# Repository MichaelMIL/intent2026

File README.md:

# INTENT 2026 Hardware Badge

RP2040 conference badge for the INTENT 2026 security summit, shaped like a vending machine: a header sign
with the lanyard holes, the cabinet with the product window, keypad and item-pickup door, and a pedestal.
56 × 100 mm, two layers, purple solder mask, with three **breakaway soda-can modules** (IR receiver,
audio jack, speaker) that snap off and plug back into slots on the badge.

Board rev **0.5** (2026-10-11). Fab target: JLCPCB, Standard PCBA.

<p align="center">
  
  &nbsp;&nbsp;&nbsp;
  
</p>

## Schematic

- **PDF:** [04-fab/intent-2026-badge-schematic.pdf](04-fab/intent-2026-badge-schematic.pdf)
- Source: [03-kicad/intent-2026-badge.kicad_sch](03-kicad/intent-2026-badge.kicad_sch) (generated, see below)

## What is on the board

| Block | Parts |
|---|---|
| MCU | RP2040 (U1), 16 Mbit QSPI flash (U2), 12 MHz crystal, BOOTSEL key SW1 |
| USB | USB-C receptacle (J1), USBLC6-2 ESD array, 27 Ω series resistors |
| Power | USB or 3×AAA battery (J3) through a P-MOSFET / Schottky power path, ME6206 3.3 V LDO |
| User interface | Keys A / B / C (GPIO4 / 3 / 2), five red "credit" LEDs (GPIO5–9), four WS2812B-2020 RGB LEDs on the shelf (GPIO10) |
| Hack header | J2, 2×13 pins (not fitted): 15 GPIO, SWD, RUN, 3V3, GND, RGB chain out; UART0 on test pads TX / RX / GND |
| Expansion slots | J5 **IR** (GPIO22), J6 **AUDIO** (GPIO11), J7 **SPK** (GPIO25). 1×3 sockets, pin 1 = GND, 2 = 3V3, 3 = signal |

### Breakaway modules

The three modules are 13 × 22 mm soda cans hanging under the pedestal on 4 mm tabs with mouse bites. Snap them off, then plug each one
into its slot. Every port has the same pinout (GND / 3V3 / signal, power in the middle), so a module plugged
in backwards swaps ground and signal and never puts 3V3 on a GPIO.

The artwork plays along: the INTENT logo, the INTENT-O-MATIC marquee, the key letters and the can rims are exposed
copper (gold with ENIG), the RGB LEDs glow inside drawn products (can, cup, chips, candy bar) on a shelf with price tags
and a dispensing coil, the keys sit in a SELECT bezel, the five red LEDs are the CREDIT meter, the module slots are the
ITEM PICKUP door, the UART test pads are the coins, and the cabinet stands on two feet. The back shows the three AAA
cells where the battery box goes, a DANGER 3V3 sticker and a service log. The modules are the vended drinks.

| Item | Module | Circuit | Slot |
|---|---|---|---|
| B1 "IR COLA" | IR | Everlight IRM-H638T 38 kHz receiver with RC supply filter | J5, GPIO22 |
| B2 "AUDIO POP" | AUDIO | 3.5 mm TRRS jack behind a 1 k / 10 n PWM low-pass and 10 µF DC block | J6, GPIO11 (PWM) |
| B3 "BEEP FIZZ" | SPK | MLT-8530 magnetic transducer, S8050 low-side driver, flyback diode | J7, GPIO25 (2.7 kHz square wave) |

## Repository layout

| Folder | Content |
|---|---|
| `00-bom/` | Priced BOM (B2) and the change log on top of it (`bom-deltas.md`, Hebrew mirror) |
| `01-spec/` | Design spec: outline, power tree, net list, GPIO map, modules |
| `02-layout/` | Placement plan, front/back mockups, logo artwork |
| `03-kicad/` | KiCad project **and the scripts that generate it** (see `BUILD-NOTES.md`) |
| `04-fab/` | Gerbers, JLC BOM/CPL, DRC/ERC reports, renders, schematic PDF, order spec |
| `05-firmware-notes/` | GPIO map and notes for the firmware |

## How the design is built

The KiCad files are generated, not hand-drawn:

- `03-kicad/scripts/design.py` is the netlist (parts, pins, nets, LCSC numbers).
- `placement.py` holds every coordinate, including the module rectangles and tabs.
- `gen_sch.py` draws the wired schematic, `pcb_build.py` creates the board and outline,
  `router/route2.py` routes it, `pcb_finish.py` adds pours and silkscreen, `fab_export.py` writes the JLC files.
- `check_sch.py --erc` proves the schematic matches `design.py` pin for pin and runs ERC.

Current status: ERC 0 errors, DRC 0 violations and 0 unconnected pads (KiCad 10.0.3).
Order details and the pre-order checklist are in [`04-fab/order-spec.md`](04-fab/order-spec.md).

## Team

Idan Ben Moshe, Matar Maoz, Benny Mizels, Michael Mark, Mattar Bernhard, Tomer Zait.

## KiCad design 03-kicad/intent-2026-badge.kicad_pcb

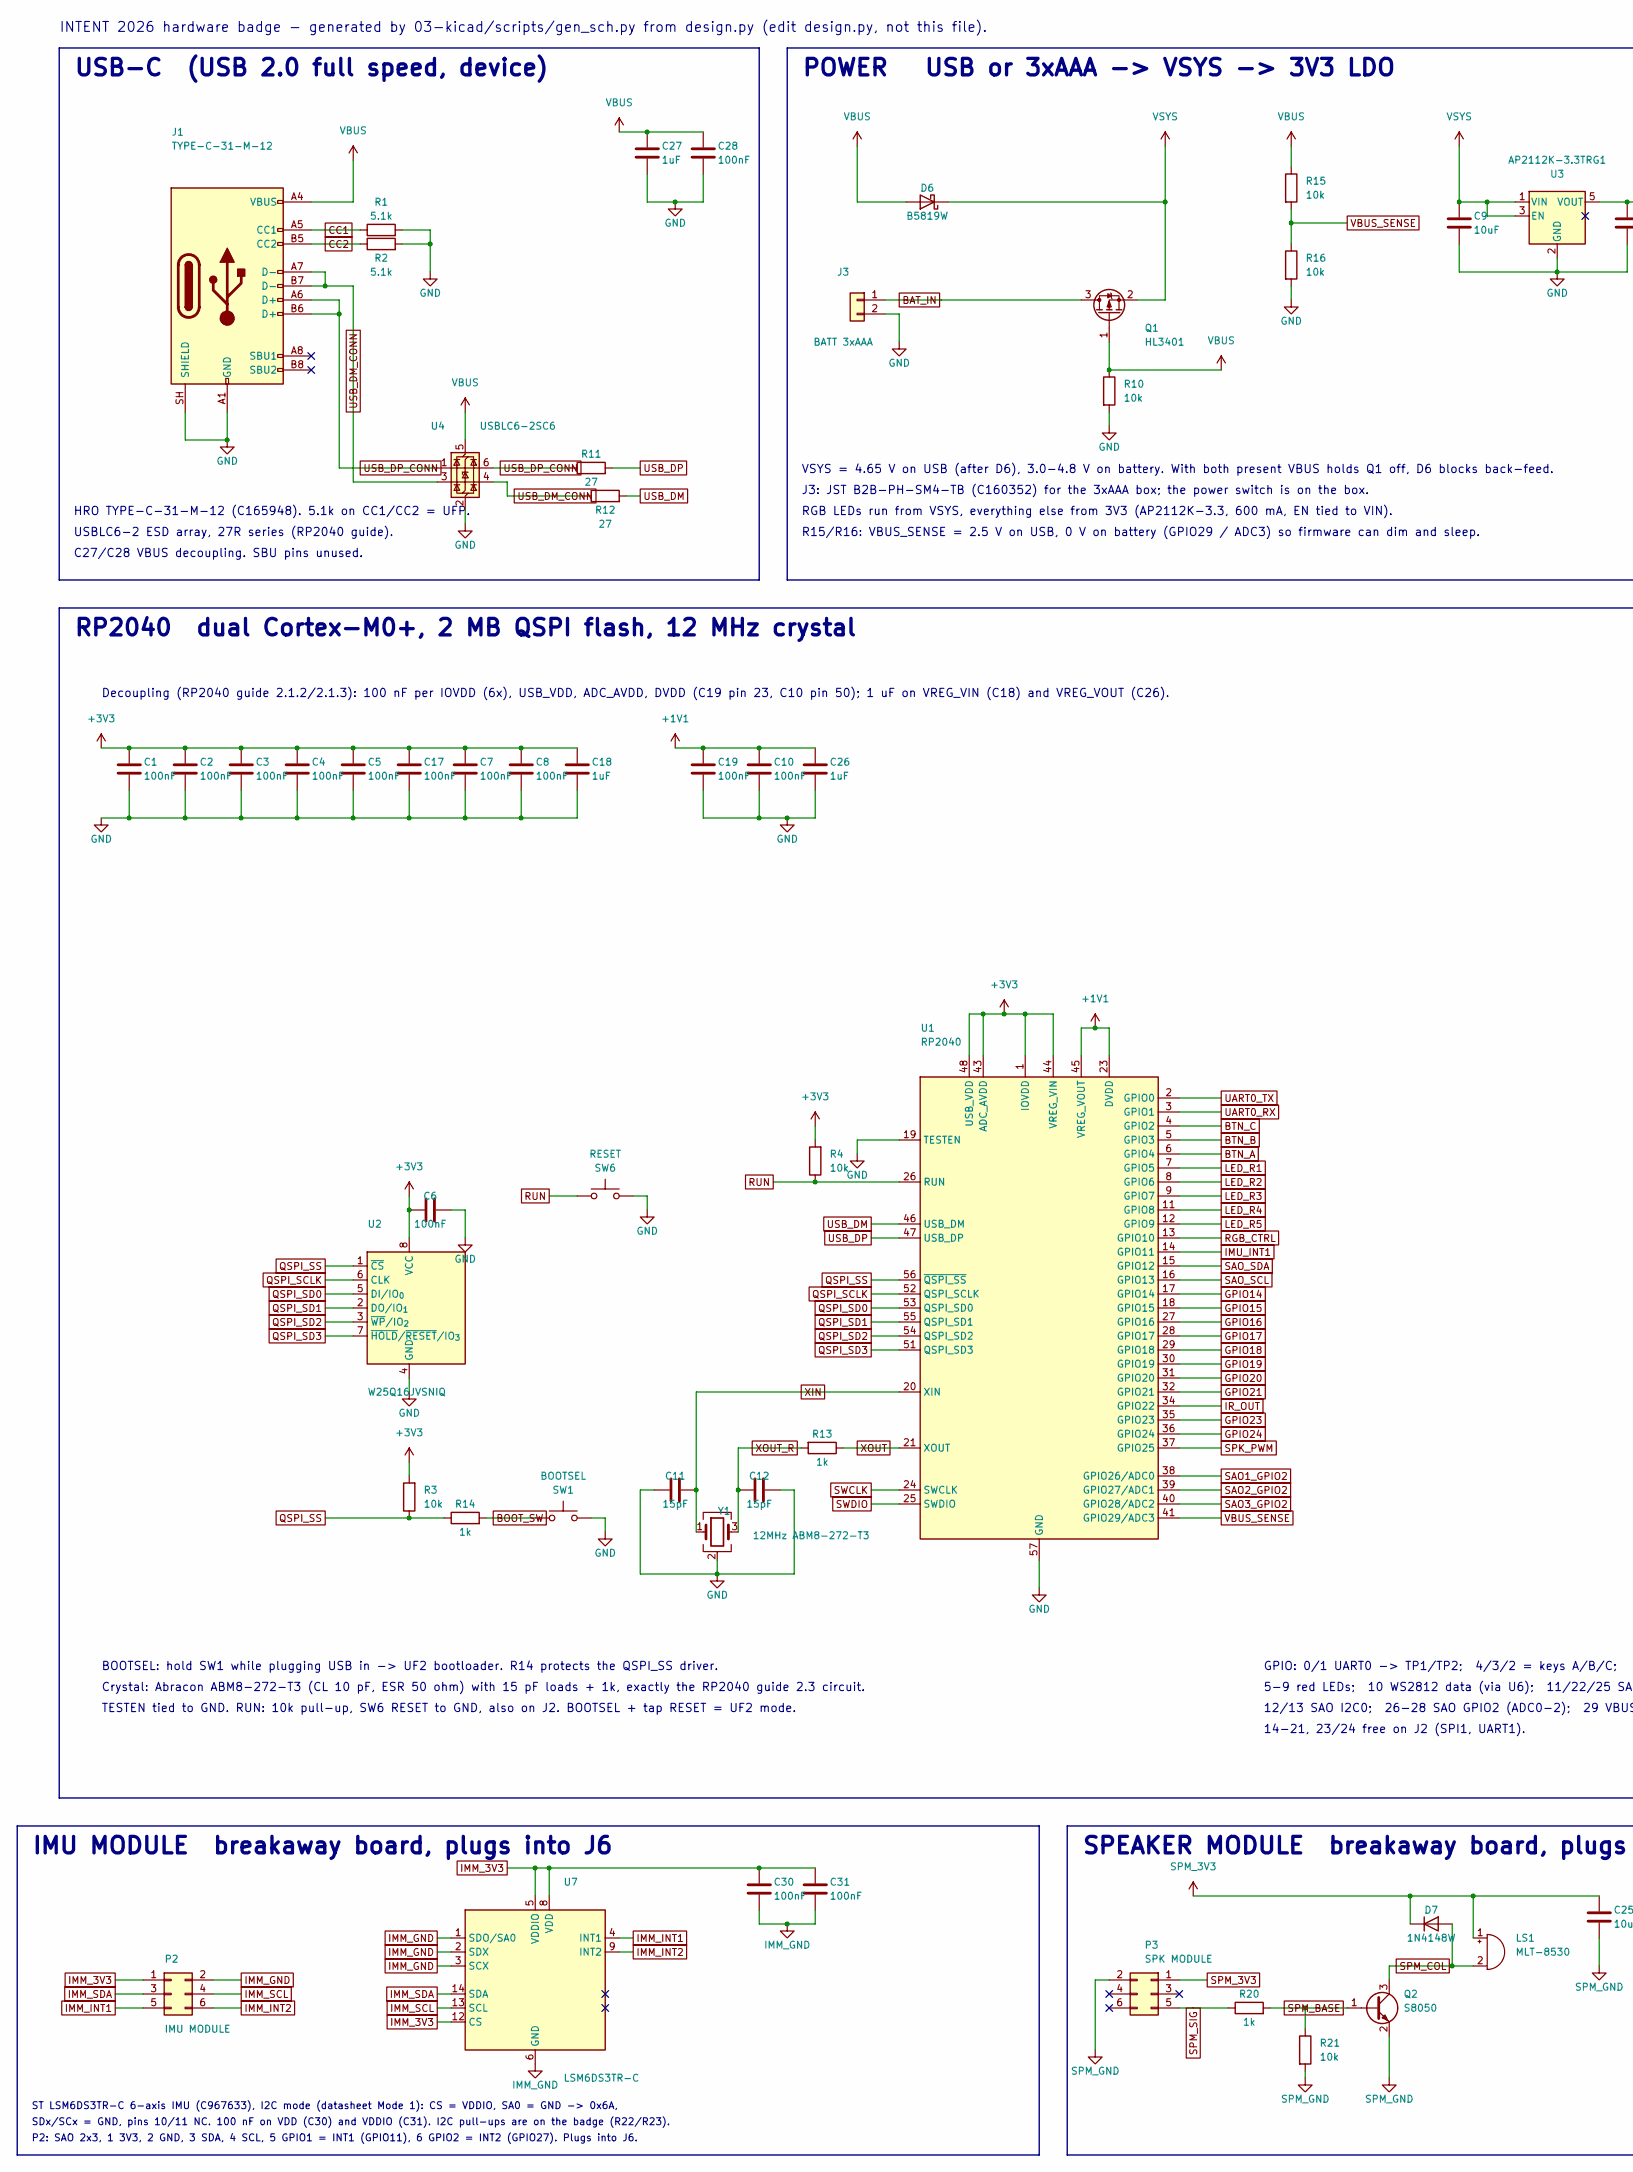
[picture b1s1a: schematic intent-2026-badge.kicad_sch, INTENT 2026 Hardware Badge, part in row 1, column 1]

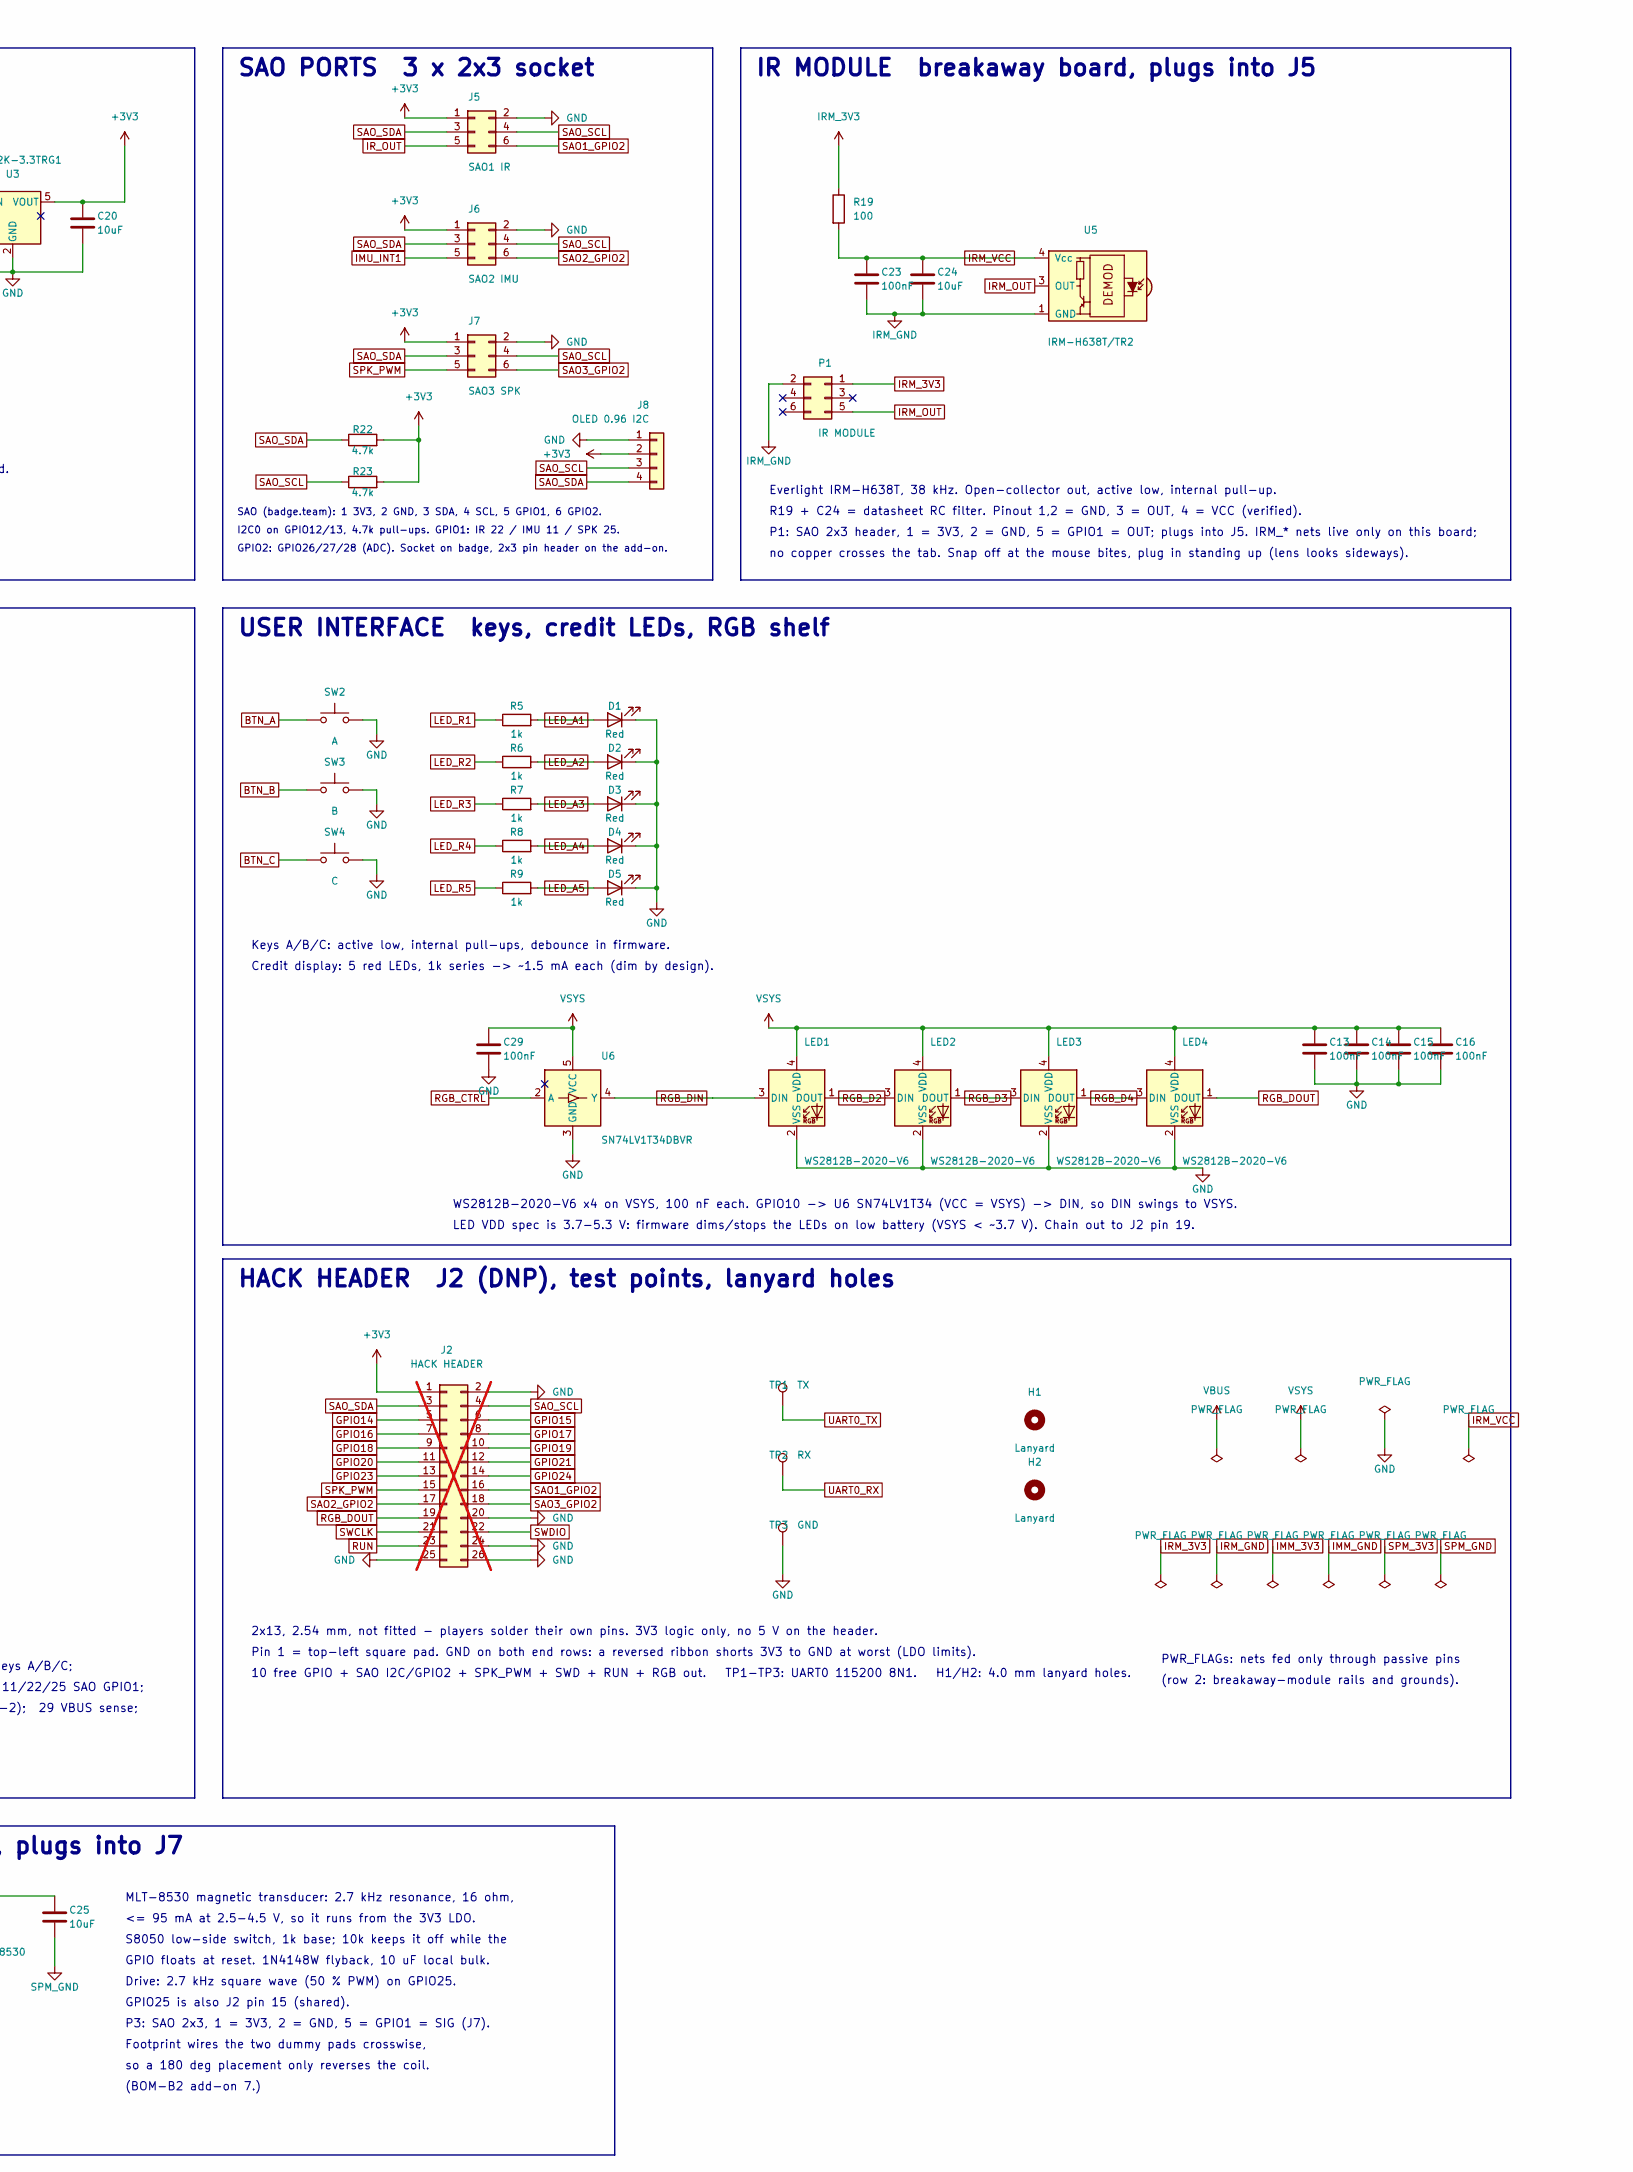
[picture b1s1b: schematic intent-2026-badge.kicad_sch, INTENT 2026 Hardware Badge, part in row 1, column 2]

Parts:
C1, C2, C3, C4, C5, C6, C7, C8, C10, C13, C14, C15, C16, C17, C19, C23, C28, C29, C30, C31: 100nF; C_0402_1005Metric; LCSC C60474
C9, C20, C24, C25: 10uF; C_0805_2012Metric; LCSC C7503495
C11, C12: 15pF; C_0402_1005Metric; LCSC C1548
C18, C26, C27: 1uF; C_0402_1005Metric; LCSC C6119792
D1, D2, D3, D4, D5: Red; LED_0603_1608Metric; LCSC C2286
D6: B5819W; D_SOD-123; LCSC C7420330
D7: 1N4148W; D_SOD-123; LCSC C81598
H1, H2: Lanyard; LanyardHole_4.0mm_Plated
J1: TYPE-C-31-M-12; USB_C_Receptacle_HRO_TYPE-C-31-M-12; LCSC C165948
J2: HACK HEADER; PinHeader_2x13_P2.54mm_Vertical; not fitted
J3: BATT 3xAAA; JST_PH_B2B-PH-SM4-TB_1x02-1MP_P2.00mm_Vertical; LCSC C160352
J5: SAO1 IR; PinSocket_2x03_P2.54mm_Vertical_SMD; LCSC C42163131
J6: SAO2 IMU; PinSocket_2x03_P2.54mm_Vertical_SMD; LCSC C42163131
J7: SAO3 SPK; PinSocket_2x03_P2.54mm_Vertical_SMD; LCSC C42163131
J8: OLED 0.96 I2C; PinSocket_1x04_P2.54mm_Vertical_SMD_Pin1Right; LCSC C42379197
LED1, LED2, LED3, LED4: WS2812B-2020-V6; LED_WS2812B-2020_PLCC4_2.0x2.0mm; LCSC C52917434
LS1: MLT-8530; Buzzer_MLT-8530_C94599; LCSC C94599
P1: IR MODULE; PinHeader_2x03_P2.54mm_Vertical_SMD; LCSC C3294461
P2: IMU MODULE; PinHeader_2x03_P2.54mm_Vertical_SMD; LCSC C3294461
P3: SPK MODULE; PinHeader_2x03_P2.54mm_Vertical_SMD; LCSC C3294461
Q1: HL3401; SOT-23; LCSC C22469449
Q2: S8050; SOT-23; LCSC C2146
R1, R2: 5.1k; R_0402_1005Metric; LCSC C25905
R3, R4, R10, R15, R16, R21: 10k; R_0402_1005Metric; LCSC C25744
R5, R6, R7, R8, R9, R13, R14, R20: 1k; R_0402_1005Metric; LCSC C11702
R11, R12: 27; R_0402_1005Metric; LCSC C25100
R19: 100; R_0402_1005Metric; LCSC C25076
R22, R23: 4.7k; R_0402_1005Metric; LCSC C25900
SW1: BOOTSEL; SW_Push_1P1T_XKB_TS-1187A; LCSC C318884
SW2: A; SW_Push_1P1T_XKB_TS-1187A; LCSC C318884
SW3: B; SW_Push_1P1T_XKB_TS-1187A; LCSC C318884
SW4: C; SW_Push_1P1T_XKB_TS-1187A; LCSC C318884
SW6: RESET; SW_Push_1P1T_XKB_TS-1187A; LCSC C318884
TP1: TX; TestPoint_THTPad_D1.5mm_Drill0.7mm
TP2: RX; TestPoint_THTPad_D1.5mm_Drill0.7mm
TP3: GND; TestPoint_THTPad_D1.5mm_Drill0.7mm
U1: RP2040; QFN-56-1EP_7x7mm_P0.4mm_EP3.2x3.2mm; LCSC C2040
U2: W25Q16JVSNIQ; SOIC-8_3.9x4.9mm_P1.27mm; LCSC C2456211
U3: AP2112K-3.3TRG1; SOT-23-5; LCSC C51118
U4: USBLC6-2SC6; SOT-23-6; LCSC C2827654
U5: IRM-H638T/TR2; IRM-H638T_C91447; LCSC C91447
U6: SN74LV1T34DBVR; SOT-23-5; LCSC C100024
U7: LSM6DS3TR-C; LGA-14_3x2.5mm_P0.5mm_LayoutBorder3x4y; LCSC C967633
Y1: 12MHz ABM8-272-T3; Crystal_SMD_3225-4Pin_3.2x2.5mm; LCSC C20625731

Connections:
+1V1: C10.1, C19.1, C26.1, U1.23 (DVDD), U1.45 (VREG_VOUT), U1.50 (DVDD)
+3V3: C1.1, C2.1, C3.1, C4.1, C5.1, C6.1, C7.1, C8.1, C17.1, C18.1, C20.1, J2.1, J5.1, J6.1, J7.1, J8.2, R3.2, R4.2, R22.2, R23.2, U1.1 (IOVDD), U1.10 (IOVDD), U1.22 (IOVDD), U1.33 (IOVDD), U1.42 (IOVDD), U1.43 (ADC_AVDD), U1.44 (VREG_VIN), U1.48 (USB_VDD), U1.49 (IOVDD), U2.8 (VCC), U3.5 (VOUT)
BAT_IN: J3.1, Q1.3 (D)
BOOT_SW: R14.2, SW1.1
BTN_A: SW2.1, U1.6 (GPIO4)
BTN_B: SW3.1, U1.5 (GPIO3)
BTN_C: SW4.1, U1.4 (GPIO2)
CC1: J1.A5 (CC1), R1.1
CC2: J1.B5 (CC2), R2.1
GND: C1.2, C2.2, C3.2, C4.2, C5.2, C6.2, C7.2, C8.2, C9.2, C10.2, C11.2, C12.2, C13.2, C14.2, C15.2, C16.2, C17.2, C18.2, C19.2, C20.2, C26.2, C27.2, C28.2, C29.2, D1.1 (K), D2.1 (K), D3.1 (K), D4.1 (K), D5.1 (K), J1.A1 (GND), J1.A12 (GND), J1.B1 (GND), J1.B12 (GND), J1.SH (SHIELD), J2.2, J2.20, J2.24, J2.25, J2.26, J3.2, J5.2, J6.2, J7.2, J8.1, LED1.2 (VSS), LED2.2 (VSS), LED3.2 (VSS), LED4.2 (VSS), R1.2, R2.2, R10.2, R16.2, SW1.2, SW2.2, SW3.2, SW4.2, SW6.2, TP3.1 (1_1), U1.19 (TESTEN), U1.57 (GND), U2.4 (GND), U3.2 (GND), U4.2 (GND), U6.3 (GND), Y1.2 (G), Y1.4 (G)
GPIO14: J2.5, U1.17 (GPIO14)
GPIO15: J2.6, U1.18 (GPIO15)
GPIO16: J2.7, U1.27 (GPIO16)
GPIO17: J2.8, U1.28 (GPIO17)
GPIO18: J2.9, U1.29 (GPIO18)
GPIO19: J2.10, U1.30 (GPIO19)
GPIO20: J2.11, U1.31 (GPIO20)
GPIO21: J2.12, U1.32 (GPIO21)
GPIO23: J2.13, U1.35 (GPIO23)
GPIO24: J2.14, U1.36 (GPIO24)
IMM_3V3: C30.1, C31.1, P2.1, U7.5 (VDDIO), U7.8 (VDD), U7.12 (CS)
IMM_GND: C30.2, C31.2, P2.2, U7.1 (SDO/SA0), U7.2 (SDX), U7.3 (SCX), U7.6 (GND), U7.7 (GND)
IMM_INT1: P2.5, U7.4 (INT1)
IMM_INT2: P2.6, U7.9 (INT2)
IMM_SCL: P2.4, U7.13 (SCL)
IMM_SDA: P2.3, U7.14 (SDA)
IMU_INT1: J6.5, U1.14 (GPIO11)
IRM_3V3: P1.1, R19.1
IRM_GND: C23.2, C24.2, P1.2, U5.1 (GND), U5.2 (GND)
IRM_OUT: P1.5, U5.3 (OUT)
IRM_VCC: C23.1, C24.1, R19.2, U5.4 (Vcc)
IR_OUT: J5.5, U1.34 (GPIO22)
LED_A1: D1.2 (A), R5.2
LED_A2: D2.2 (A), R6.2
LED_A3: D3.2 (A), R7.2
LED_A4: D4.2 (A), R8.2
LED_A5: D5.2 (A), R9.2
LED_R1: R5.1, U1.7 (GPIO5)
LED_R2: R6.1, U1.8 (GPIO6)
LED_R3: R7.1, U1.9 (GPIO7)
LED_R4: R8.1, U1.11 (GPIO8)
LED_R5: R9.1, U1.12 (GPIO9)
QSPI_SCLK: U1.52 (QSPI_SCLK), U2.6 (CLK)
QSPI_SD0: U1.53 (QSPI_SD0), U2.5 (DI/IO_{0})
QSPI_SD1: U1.55 (QSPI_SD1), U2.2 (DO/IO_{1})
QSPI_SD2: U1.54 (QSPI_SD2), U2.3 (~WP/IO_{2})
QSPI_SD3: U1.51 (QSPI_SD3), U2.7 (~HOLD/~RESET/IO_{3})
QSPI_SS: R3.1, R14.1, U1.56 (~QSPI_SS), U2.1 (~CS)
RGB_CTRL: U1.13 (GPIO10), U6.2 (A)
RGB_D2: LED1.1 (DOUT), LED2.3 (DIN)
RGB_D3: LED2.1 (DOUT), LED3.3 (DIN)
RGB_D4: LED3.1 (DOUT), LED4.3 (DIN)
RGB_DIN: LED1.3 (DIN), U6.4 (Y)
RGB_DOUT: J2.19, LED4.1 (DOUT)
RUN: J2.23, R4.1, SW6.1, U1.26 (RUN)
SAO1_GPIO2: J2.16, J5.6, U1.38 (GPIO26/ADC0)
SAO2_GPIO2: J2.17, J6.6, U1.39 (GPIO27/ADC1)
SAO3_GPIO2: J2.18, J7.6, U1.40 (GPIO28/ADC2)
SAO_SCL: J2.4, J5.4, J6.4, J7.4, J8.3, R23.1, U1.16 (GPIO13)
SAO_SDA: J2.3, J5.3, J6.3, J7.3, J8.4, R22.1, U1.15 (GPIO12)
SPK_PWM: J2.15, J7.5, U1.37 (GPIO25)
SPM_3V3: C25.1, D7.1 (K), LS1.1 (+), P3.1
SPM_BASE: Q2.1 (B), R20.2, R21.1
SPM_COL: D7.2 (A), LS1.2 (-), Q2.3 (C)
SPM_GND: C25.2, P3.2, Q2.2 (E), R21.2
SPM_SIG: P3.5, R20.1
SWCLK: J2.21, U1.24 (SWCLK)
SWDIO: J2.22, U1.25 (SWDIO)
UART0_RX: TP2.1 (1_1), U1.3 (GPIO1)
UART0_TX: TP1.1 (1_1), U1.2 (GPIO0)
USB_DM: R12.2, U1.46 (USB_DM)
USB_DM_CONN: J1.A7 (D-), J1.B7 (D-), R12.1, U4.3 (I/O2), U4.4 (I/O2)
USB_DP: R11.2, U1.47 (USB_DP)
USB_DP_CONN: J1.A6 (D+), J1.B6 (D+), R11.1, U4.1 (I/O1), U4.6 (I/O1)
VBUS: C27.1, C28.1, D6.2 (A), J1.A4 (VBUS), J1.A9 (VBUS), J1.B4 (VBUS), J1.B9 (VBUS), Q1.1 (G), R10.1, R15.1, U4.5 (VBUS)
VBUS_SENSE: R15.2, R16.1, U1.41 (GPIO29/ADC3)
VSYS: C9.1, C13.1, C14.1, C15.1, C16.1, C29.1, D6.1 (K), LED1.4 (VDD), LED2.4 (VDD), LED3.4 (VDD), LED4.4 (VDD), Q1.2 (S), U3.1 (VIN), U3.3 (EN), U6.5 (VCC)
XIN: C11.1, U1.20 (XIN), Y1.1
XOUT: R13.1, U1.21 (XOUT)
XOUT_R: C12.1, R13.2, Y1.3

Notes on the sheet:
USB-C (USB 2.0 full speed, device)
HRO TYPE-C-31-M-12 (C165948). 5.1k on CC1/CC2 = UFP.
USBLC6-2 ESD array, 27R series (RP2040 guide).
C27/C28 VBUS decoupling. SBU pins unused.
POWER USB or 3xAAA -> VSYS -> 3V3 LDO
VSYS = 4.65 V on USB (after D6), 3.0-4.8 V on battery. With both present VBUS holds Q1 off, D6 blocks back-feed.
J3: JST B2B-PH-SM4-TB (C160352) for the 3xAAA box; the power switch is on the box.
RGB LEDs run from VSYS, everything else from 3V3 (AP2112K-3.3, 600 mA, EN tied to VIN).
R15/R16: VBUS_SENSE = 2.5 V on USB, 0 V on battery (GPIO29 / ADC3) so firmware can dim and sleep.
SAO PORTS 3 x 2x3 socket
SAO (badge.team): 1 3V3, 2 GND, 3 SDA, 4 SCL, 5 GPIO1, 6 GPIO2.
I2C0 on GPIO12/13, 4.7k pull-ups. GPIO1: IR 22 / IMU 11 / SPK 25.
GPIO2: GPIO26/27/28 (ADC). Socket on badge, 2x3 pin header on the add-on.
IR MODULE breakaway board, plugs into J5
Everlight IRM-H638T, 38 kHz. Open-collector out, active low, internal pull-up.
R19 + C24 = datasheet RC filter. Pinout 1,2 = GND, 3 = OUT, 4 = VCC (verified).
P1: SAO 2x3 header, 1 = 3V3, 2 = GND, 5 = GPIO1 = OUT; plugs into J5. IRM_* nets live only on this board;
no copper crosses the tab. Snap off at the mouse bites, plug in standing up (lens looks sideways).
RP2040 dual Cortex-M0+, 2 MB QSPI flash, 12 MHz crystal
Decoupling (RP2040 guide 2.1.2/2.1.3): 100 nF per IOVDD (6x), USB_VDD, ADC_AVDD, DVDD (C19 pin 23, C10 pin 50); 1 uF on VREG_VIN (C18) and VREG_VOUT (C26).
BOOTSEL: hold SW1 while plugging USB in -> UF2 bootloader. R14 protects the QSPI_SS driver.
Crystal: Abracon ABM8-272-T3 (CL 10 pF, ESR 50 ohm) with 15 pF loads + 1k, exactly the RP2040 guide 2.3 circuit.
TESTEN tied to GND. RUN: 10k pull-up, SW6 RESET to GND, also on J2. BOOTSEL + tap RESET = UF2 mode.
GPIO: 0/1 UART0 -> TP1/TP2; 4/3/2 = keys A/B/C;
5-9 red LEDs; 10 WS2812 data (via U6); 11/22/25 SAO GPIO1;
12/13 SAO I2C0; 26-28 SAO GPIO2 (ADC0-2); 29 VBUS sense;
14-21, 23/24 free on J2 (SPI1, UART1).
USER INTERFACE keys, credit LEDs, RGB shelf
Keys A/B/C: active low, internal pull-ups, debounce in firmware.
Credit display: 5 red LEDs, 1k series -> ~1.5 mA each (dim by design).
WS2812B-2020-V6 x4 on VSYS, 100 nF each. GPIO10 -> U6 SN74LV1T34 (VCC = VSYS) -> DIN, so DIN swings to VSYS.
LED VDD spec is 3.7-5.3 V: firmware dims/stops the LEDs on low battery (VSYS < ~3.7 V). Chain out to J2 pin 19.
HACK HEADER J2 (DNP), test points, lanyard holes
2x13, 2.54 mm, not fitted - players solder their own pins. 3V3 logic only, no 5 V on the header.
Pin 1 = top-left square pad. GND on both end rows: a reversed ribbon shorts 3V3 to GND at worst (LDO limits).
10 free GPIO + SAO I2C/GPIO2 + SPK_PWM + SWD + RUN + RGB out. TP1-TP3: UART0 115200 8N1. H1/H2: 4.0 mm lanyard holes.
PWR_FLAGs: nets fed only through passive pins
(row 2: breakaway-module rails and grounds).
IMU MODULE breakaway board, plugs into J6
ST LSM6DS3TR-C 6-axis IMU (C967633), I2C mode (datasheet Mode 1): CS = VDDIO, SA0 = GND -> 0x6A,

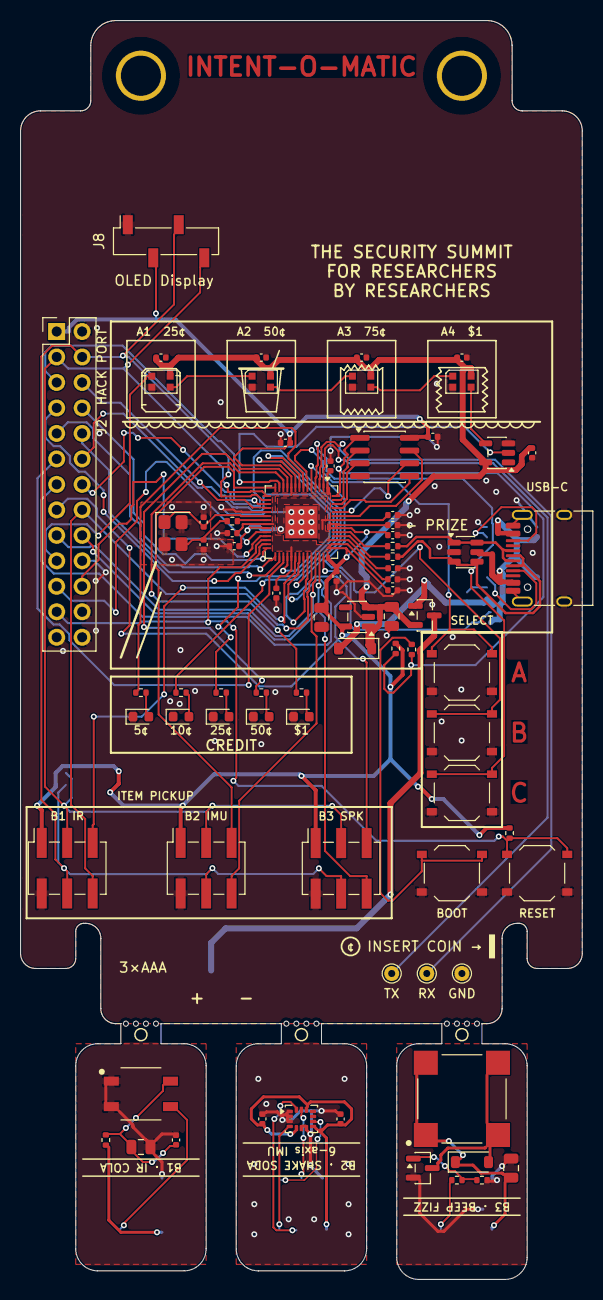
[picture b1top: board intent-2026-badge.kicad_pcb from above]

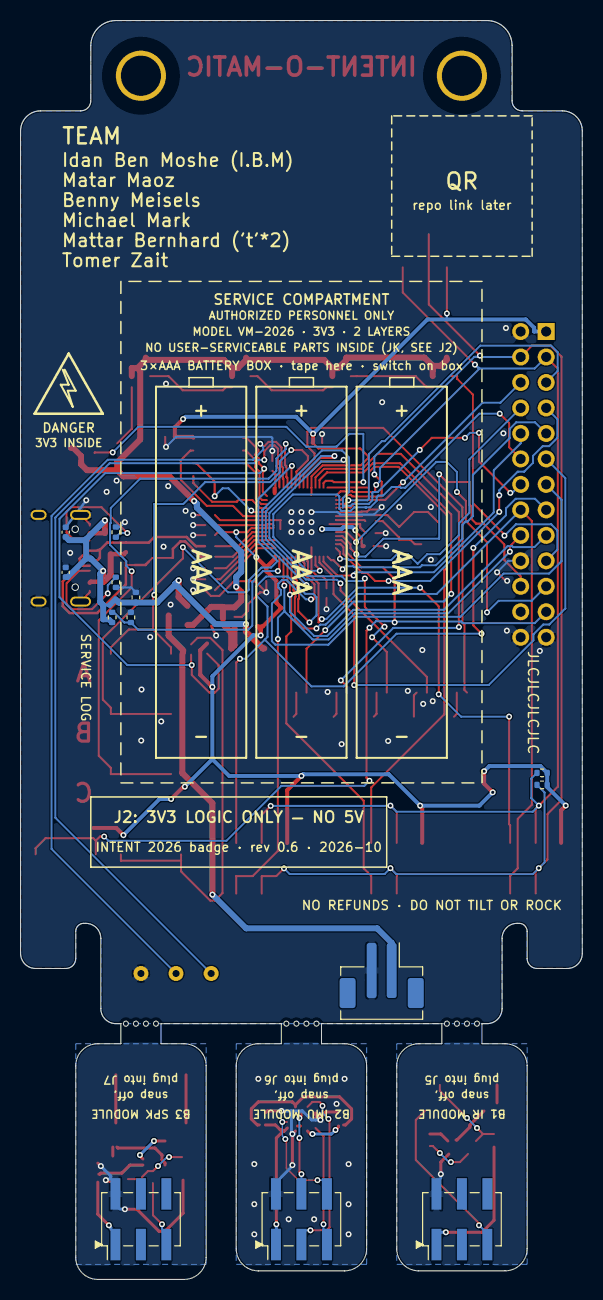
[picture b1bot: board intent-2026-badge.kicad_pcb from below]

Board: 2 copper layers, 56.0 x 125.5 mm, 95 parts (13 on the bottom side), 80 nets.

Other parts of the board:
MB1: tab IR; MouseBites_1x4_D0.5_P1.0
MB2: tab AUDIO; MouseBites_1x4_D0.5_P1.0
MB3: tab SPK; MouseBites_1x4_D0.5_P1.0

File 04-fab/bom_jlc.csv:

Comment,Designator,Footprint,LCSC Part #
100nF,"C1,C2,C3,C4,C5,C6,C7,C8,C10,C13,C14,C15,C16,C17,C19,C23,C28,C29,C30,C31",C_0402_1005Metric,C60474
10uF,"C9,C20,C24,C25",C_0805_2012Metric,C7503495
15pF,"C11,C12",C_0402_1005Metric,C1548
1uF,"C18,C26,C27",C_0402_1005Metric,C6119792
Red,"D1,D2,D3,D4,D5",LED_0603_1608Metric,C2286
B5819W,D6,D_SOD-123,C7420330
1N4148W,D7,D_SOD-123,C81598
TYPE-C-31-M-12,J1,USB_C_Receptacle_HRO_TYPE-C-31-M-12,C165948
BATT 3xAAA,J3,JST_PH_B2B-PH-SM4-TB_1x02-1MP_P2.00mm_Vertical,C160352
SAO socket 2x3 2.54mm SMD,"J5,J6,J7",PinSocket_2x03_P2.54mm_Vertical_SMD,C42163131
OLED 0.96 I2C,J8,PinSocket_1x04_P2.54mm_Vertical_SMD_Pin1Right,C42379197
WS2812B-2020-V6,"LED1,LED2,LED3,LED4",LED_WS2812B-2020_PLCC4_2.0x2.0mm,C52917434
MLT-8530,LS1,Buzzer_MLT-8530_C94599,C94599
SAO pin header 2x3 2.54mm SMD,"P1,P2,P3",PinHeader_2x03_P2.54mm_Vertical_SMD,C3294461
HL3401,Q1,SOT-23,C22469449
S8050,Q2,SOT-23,C2146
5.1k,"R1,R2",R_0402_1005Metric,C25905
10k,"R3,R4,R10,R15,R16,R21",R_0402_1005Metric,C25744
1k,"R5,R6,R7,R8,R9,R13,R14,R20",R_0402_1005Metric,C11702
27,"R11,R12",R_0402_1005Metric,C25100
100,R19,R_0402_1005Metric,C25076
4.7k,"R22,R23",R_0402_1005Metric,C25900
TS-1187A-B-A-B tactile 5.1x5.1,"SW1,SW2,SW3,SW4,SW6",SW_Push_1P1T_XKB_TS-1187A,C318884
RP2040,U1,QFN-56-1EP_7x7mm_P0.4mm_EP3.2x3.2mm,C2040
W25Q16JVSNIQ,U2,SOIC-8_3.9x4.9mm_P1.27mm,C2456211
AP2112K-3.3TRG1,U3,SOT-23-5,C51118
USBLC6-2SC6,U4,SOT-23-6,C2827654
IRM-H638T/TR2,U5,IRM-H638T_C91447,C91447
SN74LV1T34DBVR,U6,SOT-23-5,C100024
LSM6DS3TR-C,U7,LGA-14_3x2.5mm_P0.5mm_LayoutBorder3x4y,C967633
12MHz ABM8-272-T3,Y1,Crystal_SMD_3225-4Pin_3.2x2.5mm,C20625731

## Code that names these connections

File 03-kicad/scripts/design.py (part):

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  * VBUS decoupling C27 1 uF + C28 100 nF (none before); reset button SW6 on RUN
  * RGB data buffer U6 SN74LV1T34 (C100024) on VSYS: DIN swings to VSYS, fixes VIH = 0.7 x VDD at any VSYS
  * Expansion ports -> SAO (badge.team): 2x3 socket J5-J7, 2x3 header P1-P3; pinout 1 3V3, 2 GND, 3 SDA,
    4 SCL, 5 GPIO1, 6 GPIO2. I2C0 on GPIO12/13 (4.7k pull-ups), GPIO1 = old slot signal, GPIO2 = GPIO26/27/28
  * 2026-10-29: the AUDIO module (PWM filter + 3.5 mm jack) became an IMU module: ST LSM6DS3TR-C (C967633) on the SAO
    I2C bus at 0x6A (SA0 = GND), INT1 -> SAO GPIO1 (GPIO11, net IMU_INT1), INT2 -> SAO GPIO2 (GPIO27). Nets IMM_*
  * 2026-10-18: SAO socket/header changed to SMT (C42163131 / C3294461); see bom-deltas for the keyed-connector check

rev 0.5 (2026-10-11): the IR receiver, the audio jack and a new speaker are **breakaway modules** on the same
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
# ---- MCU --------------------------------------------------------------------
gpio = {i: None for i in range(30)}
gpio.update({0: 'UART0_TX', 1: 'UART0_RX', 2: 'BTN_C', 3: 'BTN_B', 4: 'BTN_A',   # A=GPIO4 (layout order)
             5: 'LED_R1', 6: 'LED_R2', 7: 'LED_R3', 8: 'LED_R4', 9: 'LED_R5',
             10: 'RGB_CTRL', 11: 'IMU_INT1', 12: 'SAO_SDA', 13: 'SAO_SCL', 22: 'IR_OUT', 25: 'SPK_PWM',
             26: 'SAO1_GPIO2', 27: 'SAO2_GPIO2', 28: 'SAO3_GPIO2', 29: 'VBUS_SENSE'})
for i in list(range(14, 22)) + [23, 24]:
    gpio[i] = 'GPIO%d' % i
gpio_pin = {0: 2, 1: 3, 2: 4, 3: 5, 4: 6, 5: 7, 6: 8, 7: 9, 8: 11, 9: 12, 10: 13, 11: 14, 12: 15, 13: 16,
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R('R15', '10k', L_10K, 'VBUS', 'VBUS_SENSE')
R('R16', '10k', L_10K, 'VBUS_SENSE', GND)
part('J3', 'Connector_Generic:Conn_01x02', 'BATT 3xAAA', 'Connector_JST:JST_PH_B2B-PH-SM4-TB_1x02-1MP_P2.00mm_Vertical',
     'C160352', {'1': 'BAT_IN', '2': GND}, desc='Battery box plug, JST B2B-PH-SM4-TB (C160352), pin1 = +')
C('C9', '10uF', L_10U, 'VSYS', GND, fp=FP_C0805, desc='LDO input')
part('U3', 'Regulator_Linear:AP2112K-3.3', 'AP2112K-3.3TRG1', 'Package_TO_SOT_SMD:SOT-23-5', 'C51118',
     {'1': 'VSYS', '2': GND, '3': 'VSYS', '4': None, '5': '+3V3'}, desc='3V3 LDO 600 mA, EN tied to VIN')
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    C('C%d' % (13 + i), '100nF', L_100N, 'VSYS', GND, desc='LED%d VDD' % (i + 1))

# ---- expansion ports (main board): SAO (badge.team), 2x3 2.54 mm socket ---------
# 1 = 3V3, 2 = GND, 3 = SDA, 4 = SCL, 5 = GPIO1, 6 = GPIO2. Shared I2C0 bus (GPIO12/13), GPIO1 = the slot signal of
# rev 0.5, GPIO2 = GPIO26/27/28 (ADC-capable). The module side is P1-P3 below.
SAO_PORTS = (('J5', 'SAO1 IR', 'IR_OUT', 'SAO1_GPIO2'), ('J6', 'SAO2 IMU', 'IMU_INT1', 'SAO2_GPIO2'),
             ('J7', 'SAO3 SPK', 'SPK_PWM', 'SAO3_GPIO2'))
for ref, name, g1, g2 in SAO_PORTS:
    part(ref, 'Connector_Generic:Conn_02x03_Odd_Even', name, FP_SOCKET6, L_SOCKET6,
         {'1': '+3V3', '2': GND, '3': 'SAO_SDA', '4': 'SAO_SCL', '5': g1, '6': g2},
         desc='SAO port: 1 3V3, 2 GND, 3 SDA, 4 SCL, 5 GPIO1 = %s, 6 GPIO2 = %s' % (g1, g2))
R('R22', '4.7k', L_4K7, 'SAO_SDA', '+3V3', desc='I2C0 SDA pull-up')
R('R23', '4.7k', L_4K7, 'SAO_SCL', '+3V3', desc='I2C0 SCL pull-up')
# 0.96" I2C OLED module (SSD1306, 4-pin GND/VCC/SCL/SDA) on the same I2C0 bus (2026-10-29). SMD 1x4 socket, staggered
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M = 'IR'
SAO_NC = {'3': None, '4': None, '6': None}
part('P1', 'Connector_Generic:Conn_02x03_Odd_Even', 'IR MODULE', FP_PINS6, L_PINS6,
     dict(SAO_NC, **{'1': 'IRM_3V3', '2': 'IRM_GND', '5': 'IRM_OUT'}), desc='SAO add-on header (GPIO1 = OUT)', module=M)
part('U5', 'Interface_Optical:IRM-H6xxT', 'IRM-H638T/TR2', 'intent:IRM-H638T_C91447', 'C91447',
     {'1': 'IRM_GND', '2': 'IRM_GND', '3': 'IRM_OUT', '4': 'IRM_VCC'}, module=M)
R('R19', '100', L_100R, 'IRM_3V3', 'IRM_VCC', module=M)
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M = 'IMU'
part('P2', 'Connector_Generic:Conn_02x03_Odd_Even', 'IMU MODULE', FP_PINS6, L_PINS6,
     {'1': 'IMM_3V3', '2': 'IMM_GND', '3': 'IMM_SDA', '4': 'IMM_SCL', '5': 'IMM_INT1', '6': 'IMM_INT2'},
     desc='SAO add-on header: I2C to the badge, GPIO1 = INT1, GPIO2 = INT2', module=M)
# LSM6DS3TR-C in I2C mode (datasheet Mode 1): CS = VDDIO, SA0 = GND (address 0x6A), SDx/SCx = GND, pins 10/11 NC;
# 100 nF on VDD and on VDDIO (datasheet note 1). SDA/SCL pull-ups are on the badge (R22/R23).
part('U7', 'Sensor_Motion:LSM6DS3', 'LSM6DS3TR-C', 'Package_LGA:LGA-14_3x2.5mm_P0.5mm_LayoutBorder3x4y', 'C967633',
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# ---- speaker module (breakaway, nets SPM_*) — BOM-B2 add-on 7 ---------------------
M = 'SPK'
part('P3', 'Connector_Generic:Conn_02x03_Odd_Even', 'SPK MODULE', FP_PINS6, L_PINS6,
     dict(SAO_NC, **{'1': 'SPM_3V3', '2': 'SPM_GND', '5': 'SPM_SIG'}), desc='SAO add-on header (GPIO1 = SIG)', module=M)
R('R20', '1k', L_1K, 'SPM_SIG', 'SPM_BASE', desc='base resistor', module=M)
R('R21', '10k', L_10K, 'SPM_BASE', 'SPM_GND', desc='keeps Q2 off while the GPIO floats', module=M)
part('Q2', 'Transistor_BJT:Q_NPN_BEC', 'S8050', 'Package_TO_SOT_SMD:SOT-23', 'C2146',
     {'1': 'SPM_BASE', '2': 'SPM_GND', '3': 'SPM_COL'}, desc='NPN low-side driver', module=M)
part('LS1', 'Device:Buzzer', 'MLT-8530', 'intent:Buzzer_MLT-8530_C94599', 'C94599',
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C('C25', '10uF', L_10U, 'SPM_3V3', 'SPM_GND', fp=FP_C0805, desc='module bulk', module=M)

# ---- header / test --------------------------------------------------------------
j2 = {1: '+3V3', 2: GND, 3: 'SAO_SDA', 4: 'SAO_SCL', 5: 'GPIO14', 6: 'GPIO15', 7: 'GPIO16', 8: 'GPIO17',
      9: 'GPIO18', 10: 'GPIO19', 11: 'GPIO20', 12: 'GPIO21', 13: 'GPIO23', 14: 'GPIO24', 15: 'SPK_PWM',
      16: 'SAO1_GPIO2', 17: 'SAO2_GPIO2', 18: 'SAO3_GPIO2', 19: 'RGB_DOUT', 20: GND, 21: 'SWCLK', 22: 'SWDIO',
      23: 'RUN', 24: GND, 25: GND, 26: GND}
part('J2', 'Connector_Generic:Conn_02x13_Odd_Even', 'HACK HEADER', 'Connector_PinHeader_2.54mm:PinHeader_2x13_P2.54mm_Vertical',
     '', {str(k): v for k, v in j2.items()}, dnp=True, in_bom=False, desc='2x13 expansion / SWD, DNP')
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PWR_FLAGS = ['GND', 'VBUS', 'VSYS', 'IRM_VCC', 'IRM_3V3', 'IRM_GND', 'IMM_3V3', 'IMM_GND', 'SPM_3V3', 'SPM_GND']

# breakaway modules: name -> ground net (zones) and the socket it mates with
MODULES = {'IR': dict(gnd='IRM_GND', socket='J5', pins='P1'),
           'IMU': dict(gnd='IMM_GND', socket='J6', pins='P2'),
           'SPK': dict(gnd='SPM_GND', socket='J7', pins='P3')}

if __name__ == '__main__':
    from collections import defaultdict
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
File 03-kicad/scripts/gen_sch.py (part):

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# D- (upper pins) and D+ (lower pins) to the ESD array; one deliberate crossing at (78.74, 101.6)
W(P('J1', 'A7'), (73.66, 66.04), (73.66, 68.58)); W(P('J1', 'B7'), (78.74, 68.58), (78.74, 104.14), (93.98, 104.14))
W(P('J1', 'A6'), (76.2, 71.12), (76.2, 73.66)); W(P('J1', 'B6'), (76.2, 73.66), (76.2, 101.6), (93.98, 101.6))
sh.label('USB_DP_CONN', 80.01, 101.6); sh.label('USB_DM_CONN', 78.74, 91.44, 90)
sh.nc(P('J1', 'A8')); sh.nc(P('J1', 'B8'))
W(P('J1', 'A1'), (55.88, 96.52)); W(P('J1', 'SH'), (48.26, 96.52), (55.88, 96.52)); sh.power('GND', 55.88, 96.52)
# VBUS decoupling (rev 0.6): 1 uF bulk + 100 nF at the connector / USBLC6 pin 5
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W(P('U4', 2), (99.06, 111.76)); sh.power('GND', 99.06, 111.76)
# pins 1/6 and 3/4 of the USBLC6 are the same line each; the labels on both sides make that explicit
put('R11', 121.92, 101.6, 90, **H); put('R12', 124.46, 106.68, 90, ref_at=(0, 2.54), val_at=(0, 5.08))
W(P('U4', 6), P('R11', 1)); sh.label('USB_DP_CONN', 105.41, 101.6)
W(P('R11', 2), (130.81, 101.6)); sh.label('USB_DP', 130.81, 101.6)
W(P('U4', 4), (106.68, 104.14), (106.68, 106.68), P('R12', 1)); sh.label('USB_DM_CONN', 107.95, 106.68)
W(P('R12', 2), (130.81, 106.68)); sh.label('USB_DM', 130.81, 106.68)
note(27.94, 110.49, 'HRO TYPE-C-31-M-12 (C165948). 5.1k on CC1/CC2 = UFP.',
     'USBLC6-2 ESD array, 27R series (RP2040 guide).',
     'C27/C28 VBUS decoupling. SBU pins unused.')
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W(P('D6', 1), (226.06, 53.34), (226.06, 43.18)); sh.power('VSYS', 226.06, 43.18)
# battery: J3 -> Q1 drain (SW5/JP1 removed 2026-10-29: the switch is on the battery box); VBUS on the gate holds Q1 off on USB
put('J3', 170.18, 71.12, mir='y', ref_at=(-2.54, -5.08), val_at=(-2.54, 7.62))
W(P('J3', 1), (185.42, 71.12)); sh.label('BAT_IN', 177.8, 71.12)
W(P('J3', 2), (177.8, 73.66), (177.8, 78.74)); sh.power('GND', 177.8, 78.74)
put('Q1', 215.9, 73.66, 90, ref_at=(6.35, 2.54), val_at=(6.35, 5.08), just=['left'])
W((185.42, 71.12), P('Q1', 3))
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# VBUS sense divider
sh.power('VBUS', 248.92, 43.18); put('R15', 248.92, 50.8, **V); put('R16', 248.92, 64.77, **V)
W((248.92, 43.18), P('R15', 1)); W(P('R15', 2), P('R16', 1)); W(P('R16', 2), (248.92, 71.12)); sh.power('GND', 248.92, 71.12)
W((248.92, 57.15), (259.08, 57.15)); sh.label('VBUS_SENSE', 259.08, 57.15)
# LDO
sh.power('VSYS', 279.4, 43.18); W((279.4, 43.18), (279.4, 53.34))
put('C9', 279.4, 57.15, **V); put('U3', 297.18, 55.88, ref_at=(0, -7.62), val_at=(0, -10.16)); put('C20', 309.88, 57.15, **V)
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note(160.02, 102.87, 'VSYS = 4.65 V on USB (after D6), 3.0-4.8 V on battery. With both present VBUS holds Q1 off, D6 blocks back-feed.',
     'J3: JST B2B-PH-SM4-TB (C160352) for the 3xAAA box; the power switch is on the box.',
     'RGB LEDs run from VSYS, everything else from 3V3 (AP2112K-3.3, 600 mA, EN tied to VIN).',
     'R15/R16: VBUS_SENSE = 2.5 V on USB, 0 V on battery (GPIO29 / ADC3) so firmware can dim and sleep.')

# =============================================================================================
# Block C - expansion ports (main board side)
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    W(P(ref, 1), (350.52, y)); sh.label(D[ref]['pins']['1'], 350.52, y, 180)
    W(P(ref, 2), (370.84, y))
W((370.84, 93.98), (370.84, 104.14)); sh.power('+3V3', 370.84, 93.98)
sh.text('SAO (badge.team): 1 3V3, 2 GND, 3 SDA, 4 SCL, 5 GPIO1, 6 GPIO2.', 337.82, 110.49, 1.27)
sh.text('I2C0 on GPIO12/13, 4.7k pull-ups. GPIO1: IR 22 / IMU 11 / SPK 25.', 337.82, 113.79, 1.27)
sh.text('GPIO2: GPIO26/27/28 (ADC). Socket on badge, 2x3 pin header on the add-on.', 337.82, 117.09, 1.27)
# J8: 0.96" I2C OLED module socket on the same bus
put('J8', 414.02, 99.06, ref_at=(-1.27, -8.89), val_at=(-1.27, -6.35), just=['right'])
p = P('J8', 1); W(p, (401.32, p[1])); sh.power('GND', 401.32, p[1], rot=270)
p = P('J8', 2); W(p, (403.86, p[1])); sh.power('+3V3', 403.86, p[1], rot=90)
p = P('J8', 3); W(p, (401.32, p[1])); sh.label('SAO_SCL', 401.32, p[1], 180)
p = P('J8', 4); W(p, (401.32, p[1])); sh.label('SAO_SDA', 401.32, p[1], 180)

# =============================================================================================
# Block D - IR module (breakaway board; nets IRM_*)
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W((447.04, 43.18), P('R19', 1)); W(P('R19', 2), (447.04, 63.5), (482.6, 63.5))
put('C23', 452.12, 67.31, **V); put('C24', 462.28, 67.31, **V)
put('U5', 492.76, 68.58, mir='y', ref_at=(0, -10.16), val_at=(0, 10.16))
sh.label('IRM_VCC', 469.9, 63.5)
W(P('C23', 2), (452.12, 73.66), P('U5', 1)); W(P('C24', 2), (462.28, 73.66)); sh.power('IRM_GND', 457.2, 73.66, lib='power:GND')
sh.label('IRM_OUT', P('U5', 3)[0], P('U5', 3)[1], 180)
put('P1', 444.5, 88.9, mir='y', ref_at=(-1.27, -6.35), val_at=(-1.27, 6.35), just=['left'])
p = P('P1', 1); W(p, (457.2, p[1])); sh.label('IRM_3V3', 457.2, p[1])
p = P('P1', 5); W(p, (457.2, p[1])); sh.label('IRM_OUT', 457.2, p[1])
p = P('P1', 2); W(p, (434.34, p[1]), (434.34, 96.52)); sh.power('IRM_GND', 434.34, 96.52, lib='power:GND')
for pn in (3, 4, 6):
    sh.nc(P('P1', pn))
note(434.34, 106.68, 'Everlight IRM-H638T, 38 kHz. Open-collector out, active low, internal pull-up.',
     'R19 + C24 = datasheet RC filter. Pinout 1,2 = GND, 3 = OUT, 4 = VCC (verified).',
     'P1: SAO 2x3 header, 1 = 3V3, 2 = GND, 5 = GPIO1 = OUT; plugs into J5. IRM_* nets live only on this board;',
     'no copper crosses the tab. Snap off at the mouse bites, plug in standing up (lens looks sideways).')

# =============================================================================================
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# TESTEN, RUN
W(P('U1', 19), (170.18, 223.52), (170.18, 226.06)); sh.power('GND', 170.18, 226.06)
put('R4', 162.56, 227.33, 180, **V)
W(P('U1', 26), (154.94, 231.14)); sh.label('RUN', 154.94, 231.14, 180)
W(P('R4', 2), (162.56, 220.98)); sh.power('+3V3', 162.56, 220.98)
put('SW6', 124.46, 233.68, ref_at=(0, -5.08), val_at=(0, -7.62))
W(P('SW6', 1), (114.3, 233.68)); sh.label('RUN', 114.3, 233.68, 180)
W(P('SW6', 2), (132.08, 233.68), (132.08, 236.22)); sh.power('GND', 132.08, 236.22)
# USB, QSPI, SWD stubs with labels
stub_labels('U1', (46, 47, 56, 52, 53, 55, 54, 51, 24, 25), 172.72, 180)
# crystal
put('Y1', 144.78, 294.64, ref_at=(0, -3.81), val_at=(6.35, 0.64), just=['left'])
W(P('U1', 20), (140.97, 269.24), P('Y1', 1)); sh.label('XIN', 160.02, 269.24)
put('R13', 163.83, 279.4, 270, **H)
W(P('U1', 21), P('R13', 1)); sh.label('XOUT', 170.18, 279.4)
W(P('R13', 2), (148.59, 279.4), P('Y1', 3)); sh.label('XOUT_R', 151.13, 279.4)
put('C11', 137.16, 287.02, 270, **H); put('C12', 152.4, 287.02, 90, **H)
W(P('C11', 2), (130.81, 287.02), (130.81, 302.26), (158.75, 302.26), (158.75, 287.02), P('C12', 2))
W(P('Y1', 2), (144.78, 302.26)); sh.power('GND', 144.78, 302.26)
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W(P('U2', 8), (88.9, 233.68)); W(P('C6', 2), (99.06, 236.22), (99.06, 241.3)); sh.power('+3V3', 88.9, 233.68); sh.power('GND', 99.06, 241.3)
W(P('U2', 4), (88.9, 269.24)); sh.power('GND', 88.9, 269.24)
put('R3', 88.9, 288.29, 180, **V); put('R14', 99.06, 292.1, 90, **H); put('SW1', 116.84, 292.1, ref_at=(0, -5.08), val_at=(0, -7.62))
sh.label('QSPI_SS', 73.66, 292.1, 180); W((73.66, 292.1), P('R3', 1)); W(P('R3', 2), (88.9, 281.94)); sh.power('+3V3', 88.9, 281.94)
W(P('R3', 1), P('R14', 1)); W(P('R14', 2), P('SW1', 1)); sh.label('BOOT_SW', 104.14, 292.1)
W(P('SW1', 2), (124.46, 292.1), (124.46, 294.64)); sh.power('GND', 124.46, 294.64)
note(33.02, 320.04, 'BOOTSEL: hold SW1 while plugging USB in -> UF2 bootloader. R14 protects the QSPI_SS driver.',
     'Crystal: Abracon ABM8-272-T3 (CL 10 pF, ESR 50 ohm) with 15 pF loads + 1k, exactly the RP2040 guide 2.3 circuit.',
     'TESTEN tied to GND. RUN: 10k pull-up, SW6 RESET to GND, also on J2. BOOTSEL + tap RESET = UF2 mode.')
# GPIO stubs
stub_labels('U1', tuple(design.gpio_pin[g] for g in range(30)), 236.22, 0)
note(243.84, 320.04, 'GPIO: 0/1 UART0 -> TP1/TP2;  4/3/2 = keys A/B/C;', '5-9 red LEDs;  10 WS2812 data (via U6);  11/22/25 SAO GPIO1;',
     '12/13 SAO I2C0;  26-28 SAO GPIO2 (ADC0-2);  29 VBUS sense;', '14-21, 23/24 free on J2 (SPI1, UART1).')

# =============================================================================================
# Block F - UI
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# RGB chain
sh.power('VSYS', 434.34, 203.2); W((434.34, 203.2), (556.26, 203.2))
put('U6', 398.78, 215.9, ref_at=(5.08, -7.62), val_at=(5.08, 7.62), just=['left'])
W(P('U6', 2), (383.54, 215.9)); sh.label('RGB_CTRL', 383.54, 215.9, 180)
W(P('U6', 4), (424.18, 215.9)); sh.label('RGB_DIN', 414.02, 215.9)
sh.nc(P('U6', 1))
W(P('U6', 5), (398.78, 203.2)); sh.power('VSYS', 398.78, 203.2)
put('C29', 383.54, 207.01, **V); W((383.54, 203.2), (398.78, 203.2)); sh.power('GND', 383.54, 210.82)
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    if i:
        sh.label(chain[i], lx - 15.24, 215.9)
    W((lx - 15.24, 215.9), P(ref, 3))
W(P('LED4', 1), (523.24, 215.9)); sh.label('RGB_DOUT', 523.24, 215.9)
W((439.42, 228.6), (513.08, 228.6)); sh.power('GND', 513.08, 228.6)
for i, c in enumerate(('C13', 'C14', 'C15', 'C16')):
    x = 533.4 + 7.62 * i
    put(c, x, 207.01, **V); W(P(c, 2), (x, 213.36))
W((533.4, 213.36), (556.26, 213.36)); sh.power('GND', 541.02, 213.36)
note(376.92, 236.22, 'WS2812B-2020-V6 x4 on VSYS, 100 nF each. GPIO10 -> U6 SN74LV1T34 (VCC = VSYS) -> DIN, so DIN swings to VSYS.',
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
